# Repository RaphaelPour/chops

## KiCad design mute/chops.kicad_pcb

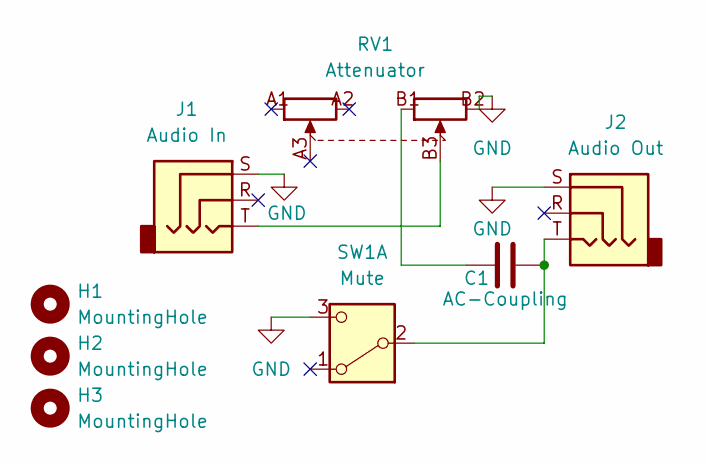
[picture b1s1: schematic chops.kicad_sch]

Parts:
C1: AC-Coupling; C_Disc_D12.5mm_W5.0mm_P7.50mm
H1, H2, H3: MountingHole; MountingHole_3.2mm_M3_DIN965
J1: Audio In; Jack_3.5mm_CUI_SJ1-3523N_Horizontal
J2: Audio Out; Jack_3.5mm_CUI_SJ1-3523N_Horizontal
RV1: Attenuator; PS45M0MC2BR10KN
SW1: Mute; SW_PUSH_E-Switch_FS5700DP_DPDT

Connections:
GND: J1.S, J2.S, RV1.B2 (OutB), SW1.3 (C)
unnamed: C1.1, RV1.B1 (GND)
unnamed: J1.T, RV1.B3 (InB)
unnamed: C1.2, J2.T, SW1.2 (B)

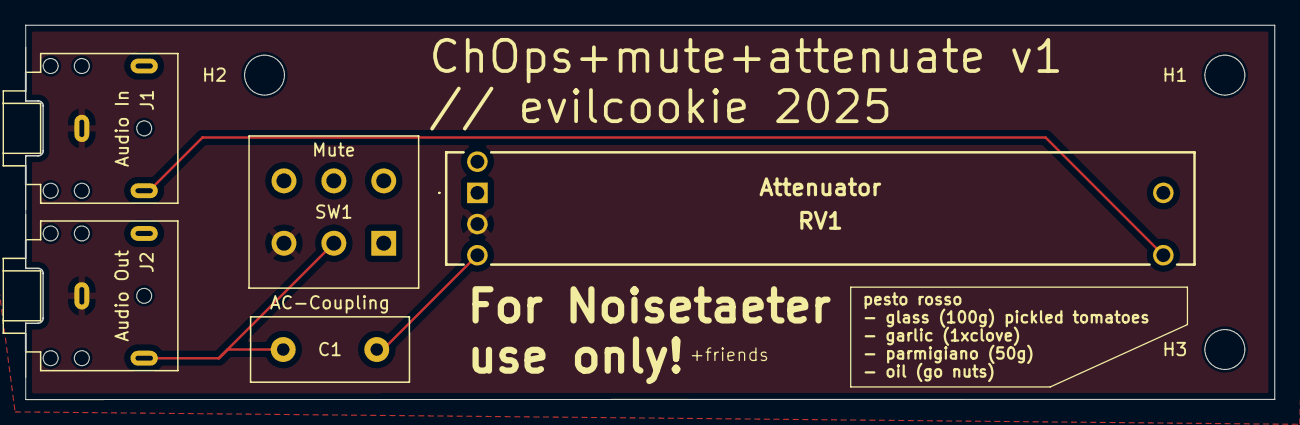
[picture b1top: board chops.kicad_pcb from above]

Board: 2 copper layers, 100.2 x 30.0 mm, 8 parts (0 on the bottom side), 4 nets.

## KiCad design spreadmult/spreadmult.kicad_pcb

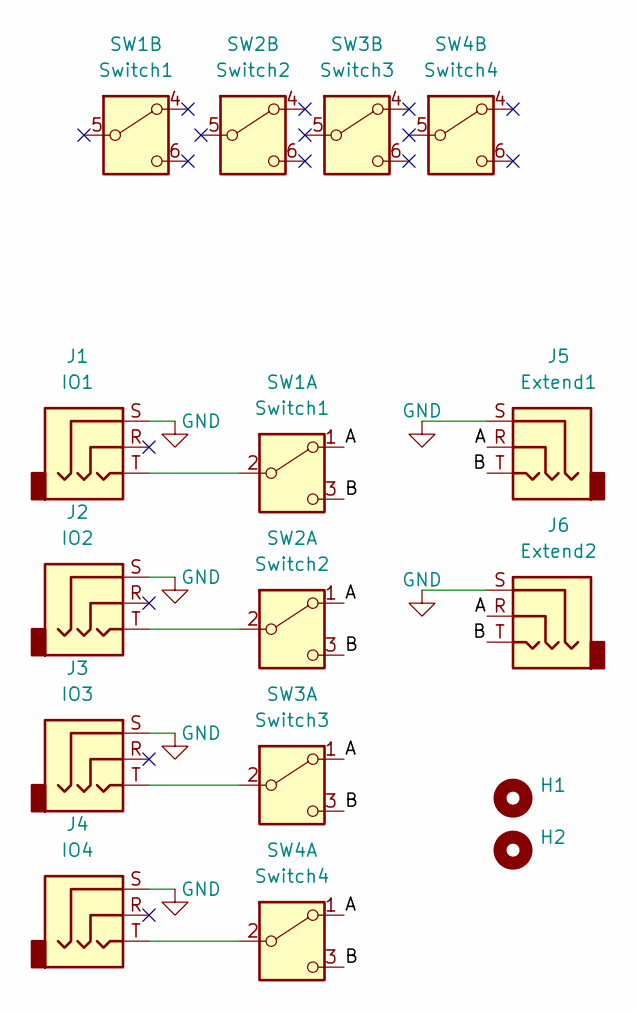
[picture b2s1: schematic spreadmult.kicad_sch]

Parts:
H1, H2: MountingHole; MountingHole_3.2mm_M3_DIN965
J1: IO1; Jack_3.5mm_CUI_SJ1-3523N_Horizontal
J2: IO2; Jack_3.5mm_CUI_SJ1-3523N_Horizontal
J3: IO3; Jack_3.5mm_CUI_SJ1-3523N_Horizontal
J4: IO4; Jack_3.5mm_CUI_SJ1-3523N_Horizontal
J5: Extend1; Jack_3.5mm_CUI_SJ1-3523N_Horizontal
J6: Extend2; Jack_3.5mm_CUI_SJ1-3523N_Horizontal
SW1: Switch1; SW_PUSH_E-Switch_FS5700DP_DPDT
SW2: Switch2; SW_PUSH_E-Switch_FS5700DP_DPDT
SW3: Switch3; SW_PUSH_E-Switch_FS5700DP_DPDT
SW4: Switch4; SW_PUSH_E-Switch_FS5700DP_DPDT

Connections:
/A: J5.R, J6.R, SW1.1 (A), SW2.1 (A), SW3.1 (A), SW4.1 (A)
/B: J5.T, J6.T, SW1.3 (C), SW2.3 (C), SW3.3 (C), SW4.3 (C)
GND: J1.S, J2.S, J3.S, J4.S, J5.S, J6.S
unnamed: J1.T, SW1.2 (B)
unnamed: J2.T, SW2.2 (B)
unnamed: J3.T, SW3.2 (B)
unnamed: J4.T, SW4.2 (B)

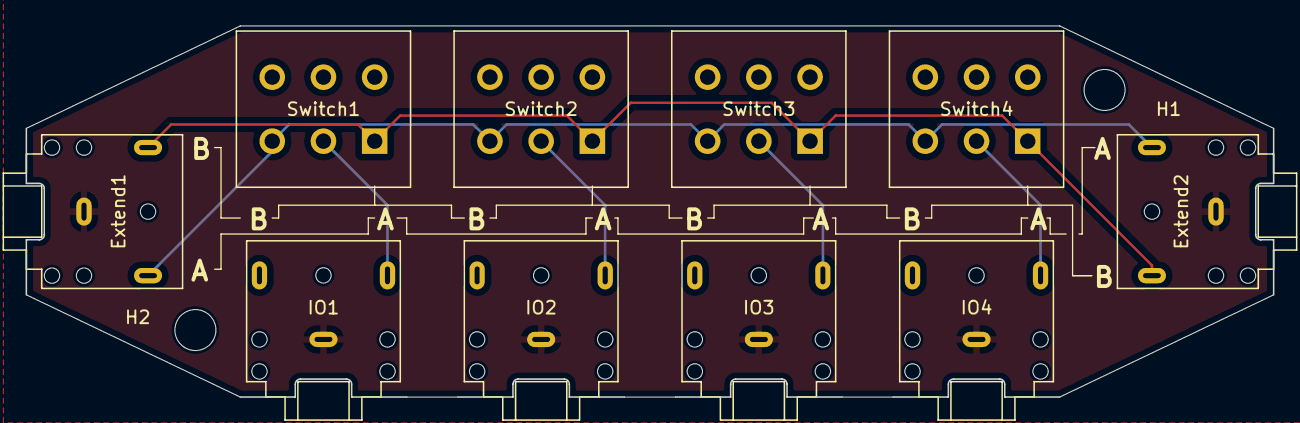
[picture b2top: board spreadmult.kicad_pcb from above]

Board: 2 copper layers, 97.4 x 29.0 mm, 12 parts (0 on the bottom side), 7 nets.

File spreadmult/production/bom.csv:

Designator,Footprint,Quantity,Value,LCSC Part #
J1,Jack_3.5mm_CUI_SJ1-3523N_Horizontal,1,IO1,
J2,Jack_3.5mm_CUI_SJ1-3523N_Horizontal,1,IO2,
J3,Jack_3.5mm_CUI_SJ1-3523N_Horizontal,1,IO3,
J4,Jack_3.5mm_CUI_SJ1-3523N_Horizontal,1,IO4,
J5,Jack_3.5mm_CUI_SJ1-3523N_Horizontal,1,Extend1,
J6,Jack_3.5mm_CUI_SJ1-3523N_Horizontal,1,Extend2,
SW1,SW_PUSH_E-Switch_FS5700DP_DPDT,1,Switch1,
SW2,SW_PUSH_E-Switch_FS5700DP_DPDT,1,Switch2,
SW3,SW_PUSH_E-Switch_FS5700DP_DPDT,1,Switch3,
SW4,SW_PUSH_E-Switch_FS5700DP_DPDT,1,Switch4,
